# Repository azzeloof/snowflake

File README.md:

# snowflake
 A PCB holiday ornament with lots of blinking LEDs!

## Hardware
The board consists of twelve reverse-mounted LEDs [charlieplexed](https://en.wikipedia.org/wiki/Charlieplexing) and hooked up to an ATtiny85. Each LED is individually addressable, even though only four of the ATtiny's pins are being used (Charlieplexing is magic)! The board also has a pushbutton for switching between modes. The ornament is powered via six CR1225 batteries.

The final board isn't the most elegant thing- there are several zero-ohm jumpers, and there's even a "decorative" wire that wraps around the snowflake that is actually a ground line I didn't want to route across the front of the ornament.

There is also a mistake in the current board files- under each LED should be a rectangle on the f.mask layer so that the area below the LED is free of solder mask. Instead, the rectangle is a keepout zone, which is useless in this situation. My solution was to scrape the areas clear with a knife but I don't recommend it because FR4 dust is nasty. The better solution is to fix the board files before ordering.

Board Front             |  Board Back
:-------------------------:|:-------------------------:
  |  

### BOM
A complete BOM can be found under [/documentation/snowflake_bom.csv](/documentation/snowflake_bom.csv), and can be uploaded to DigiKey for easy ordering. At the time of writing, the total DigiKey order is around $13. Boards can be ordered from anywhere that'll do white solder mask (I used PCBWay) and should be fairly cheap as well. You can order a stencil if desired, but I found it pretty easy to hand solder this one.

## (Firm?)(Soft?)ware
The ATtiny is programmed using the PlatformIO framework. Before programming, you need to write an Arduino bootloader to the chip using the Arduino IDE. When burning the bootloader, here are the settings we used:

+ Chip: "ATtiny85"
+ Clock: "8 MHz (internal)"
+ B.O.D: "B.O.D. Disabled"
+ Timer 1 Clock: "CPU"
+ LTO (1.6.11+ only): "Disabled"

The code is adapted from the wonderful work of David Johnson-Davies, published at http://www.technoblogy.com/show?2H0K.

To program the chips, we used SparkFun's [Pocket AVR Programmer](https://www.sparkfun.com/products/9825), but you should be able to use any programmer compatibe with the ATtiny85 (or just use an Arduino Uno!).

## Version History
Release 1.0 represents the snowflake ornaments as we initially made and distributed them. Once it is released, maybe we'll improve some stuff (but any hardware improvements will be untested).

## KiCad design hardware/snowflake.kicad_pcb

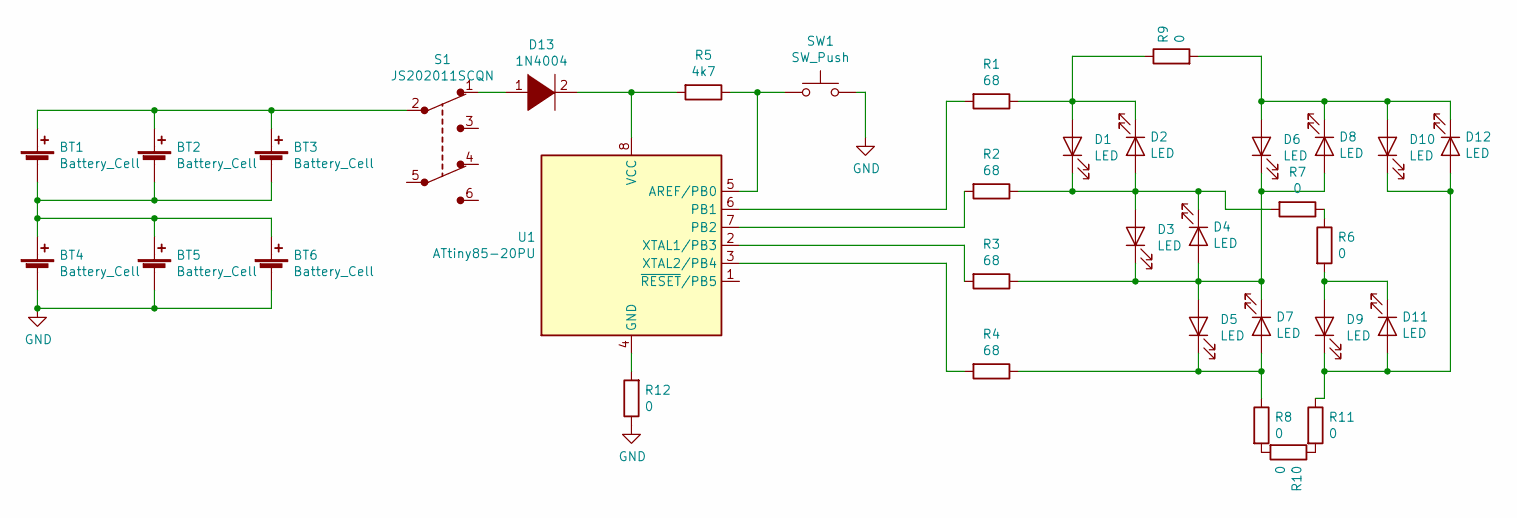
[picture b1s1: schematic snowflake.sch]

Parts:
BT1, BT2, BT3, BT4, BT5, BT6: Battery_Cell; BatteryHolder_Keystone_3000_1x12mm
D1, D2, D3, D4, D5, D6, D7, D8, D9, D10, D11, D12: LED; LED_1206_3216Metric
D13: 1N4004; D_SOD-123F
R1, R2, R3, R4: 68; R_0805_2012Metric
R5: 4k7; R_0805_2012Metric
R6, R7, R8, R9, R10, R11, R12: 0; R_0805_2012Metric
S1: JS202011SCQN; Switch_Slide_JS202011SCQN; MPN JS202011SCQN; Digi-Key_PN 401-2002-1-ND
SW1: SW_Push; SW_Push_1P1T_NO_CK_KSC6xxJ
U1: ATtiny85-20PU; DIP-8_W7.62mm_SMDSocket_SmallPads

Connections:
GND: BT4.2 (-), BT5.2 (-), BT6.2 (-), R12.1, SW1.2
unnamed: BT1.1 (+), BT2.1 (+), BT3.1 (+), S1.2
unnamed: BT1.2 (-), BT2.2 (-), BT3.2 (-), BT4.1 (+), BT5.1 (+), BT6.1 (+)
unnamed: D1.1 (K), D2.2 (A), D3.2 (A), D4.1 (K), R2.1, R7.2
unnamed: D1.2 (A), D2.1 (K), R1.1, R9.1
unnamed: D3.1 (K), D4.2 (A), D5.2 (A), D6.1 (K), D7.1 (K), D8.2 (A), R3.1
unnamed: D5.1 (K), D7.2 (A), R4.1, R8.1
unnamed: D9.1 (K), D10.1 (K), D11.2 (A), D12.2 (A), R11.1
unnamed: D6.2 (A), D8.1 (K), D10.2 (A), D12.1 (K), R9.2
unnamed: D9.2 (A), D11.1 (K), R6.2
unnamed: D13.1 (K), S1.1
unnamed: D13.2 (A), R5.2, U1.8 (VCC)
unnamed: R1.2, U1.6 (PB1)
unnamed: R2.2, U1.7 (PB2)
unnamed: R3.2, U1.2 (XTAL1/PB3)
unnamed: R4.2, U1.3 (XTAL2/PB4)
unnamed: R5.1, SW1.1, U1.5 (AREF/PB0)
unnamed: R6.1, R7.1
unnamed: R10.1, R11.2
unnamed: R8.2, R10.2
unnamed: R12.2, U1.4 (GND)

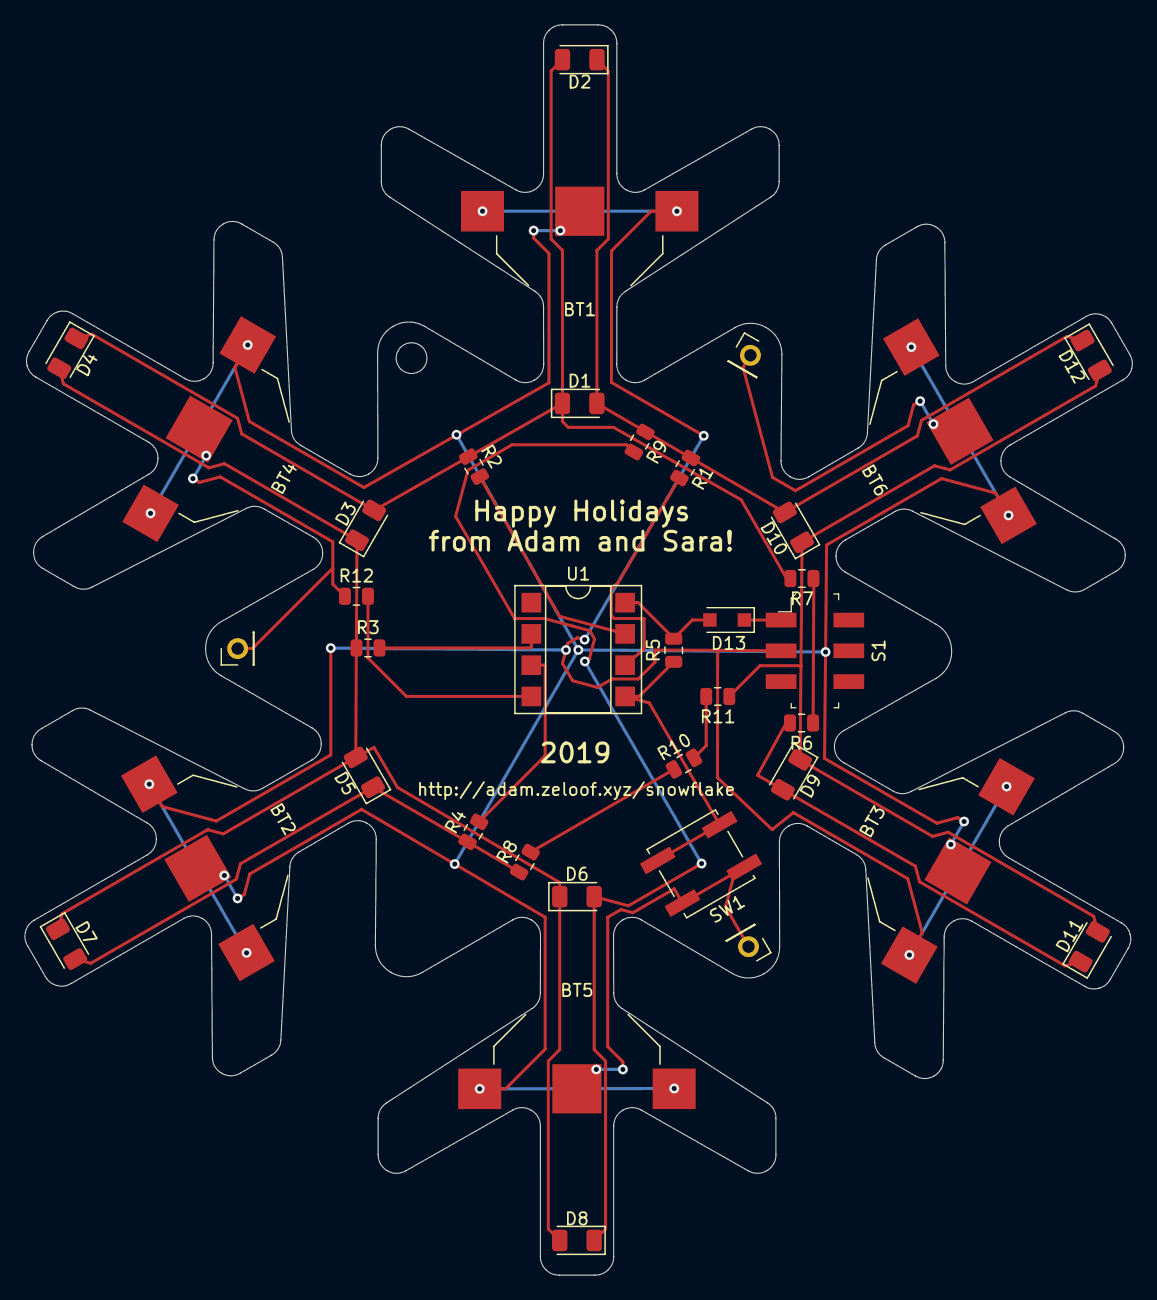
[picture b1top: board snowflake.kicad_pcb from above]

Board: 2 copper layers, 90.0 x 101.6 mm, 34 parts (0 on the bottom side), 21 nets.

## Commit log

2019-12-15 Create charlieplex_test.ino
    Code doesn't quite work yet
2019-12-16 Documentation Updates
2019-12-16 fixing indexing, log fading
2019-12-16 recognize button press
2019-12-17 adding button press functionality
2019-12-17 Added PIO migration
2019-12-17 updating pio
2019-12-17 code reorg
2019-12-17 moving headers, adding off mode
2019-12-18 Repo Restructuring
2019-12-18 added twinkle mode
2019-12-18 twinkle edits
2019-12-19 fixed twinkle stall, added chaos mode
2019-12-19 Flipped button state
2019-12-21 gitignore fix
2021-11-27 PlatformIO config fixes
    Looks like PlatformIO's Attiny85 definition changed and messed up some things. This should fix it.
